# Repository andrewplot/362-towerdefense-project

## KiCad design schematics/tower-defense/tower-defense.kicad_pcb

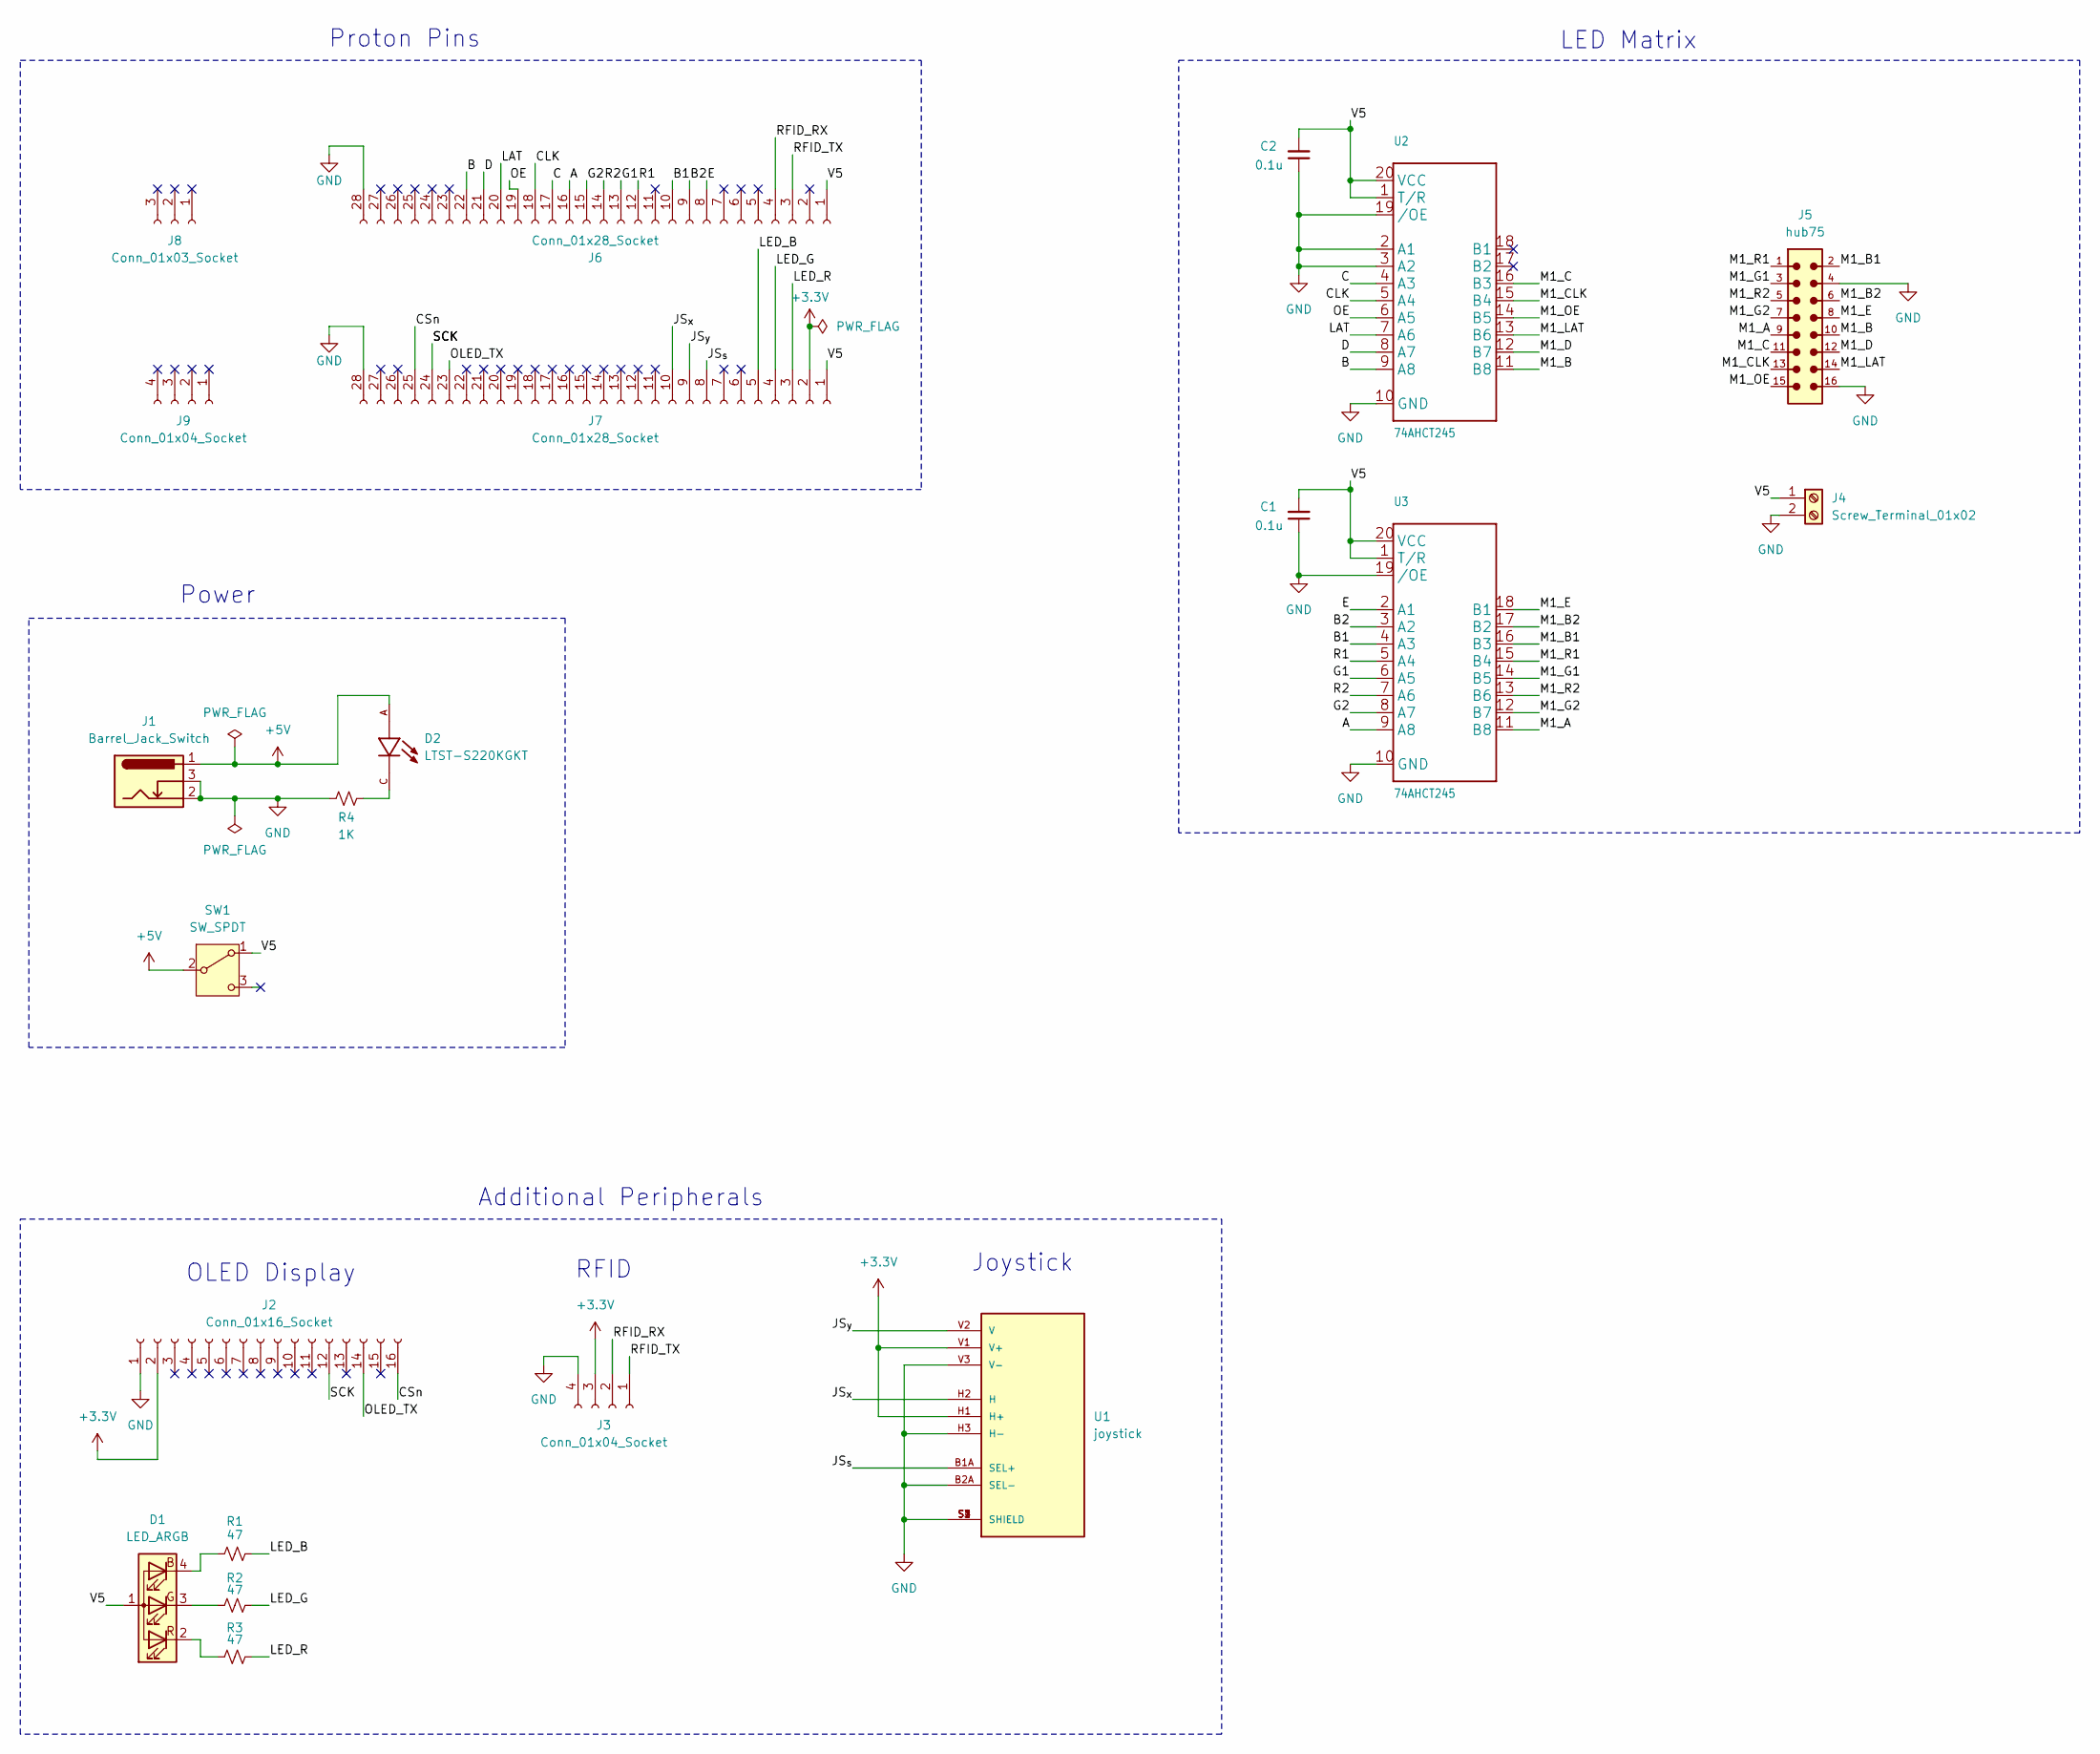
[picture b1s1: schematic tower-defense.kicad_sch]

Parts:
C1, C2: 0.1u; C_0603_1608Metric
D1: LED_ARGB; PinSocket_1x04_P2.54mm_Vertical
D2: LTST-S220KGKT; status_led; PARTREV D
J1: Barrel_Jack_Switch; barrel_jack
J2: Conn_01x16_Socket; PinSocket_1x16_P2.54mm_Vertical
J3: Conn_01x04_Socket; PinSocket_1x04_P2.54mm_Horizontal
J4: Screw_Terminal_01x02; screw-terminal
J5: hub75
J6, J7: Conn_01x28_Socket; PinSocket_1x28_P2.54mm_Vertical
J8: Conn_01x03_Socket; PinSocket_1x03_P2.54mm_Vertical
J9: Conn_01x04_Socket; PinSocket_1x04_P2.54mm_Vertical
R1, R2, R3: 47; R_0603_1608Metric
R4: 1K; R_0603_1608Metric
SW1: SW_SPDT; power_switch
U1: joystick; PARTREV N/A
U2, U3: 74AHCT245; 74HTC245

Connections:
+3.3V: J2.2, J3.3, J7.2, U1.H1 (H+), U1.V1 (V+)
+5V: D2.A, J1.1, SW1.2 (B)
/A: J6.16, U3.9 (A8)
/B: J6.22, U2.9 (A8)
/B1: J6.10, U3.4 (A3)
/B2: J6.9, U3.3 (A2)
/C: J6.17, U2.4 (A3)
/CLK: J6.18, U2.5 (A4)
/CSn: J2.16, J7.25
/D: J6.21, U2.8 (A7)
/E: J6.8, U3.2 (A1)
/G1: J6.13, U3.6 (A5)
/G2: J6.15, U3.8 (A7)
/JS_{s}: J7.8, U1.B1A (SEL+)
/JS_{x}: J7.10, U1.H2 (H)
/JS_{y}: J7.9, U1.V2 (V)
/LAT: J6.20, U2.7 (A6)
/LED_B: J7.5, R1.2
/LED_G: J7.4, R2.2
/LED_R: J7.3, R3.2
/M1_A: J5.9, U3.11 (B8)
/M1_B: J5.10, U2.11 (B8)
/M1_B1: J5.2, U3.16 (B3)
/M1_B2: J5.6, U3.17 (B2)
/M1_C: J5.11, U2.16 (B3)
/M1_CLK: J5.13, U2.15 (B4)
/M1_D: J5.12, U2.12 (B7)
/M1_E: J5.8, U3.18 (B1)
/M1_G1: J5.3, U3.14 (B5)
/M1_G2: J5.7, U3.12 (B7)
/M1_LAT: J5.14, U2.13 (B6)
/M1_OE: J5.15, U2.14 (B5)
/M1_R1: J5.1, U3.15 (B4)
/M1_R2: J5.5, U3.13 (B6)
/OE: J6.19, U2.6 (A5)
/OLED_TX: J2.14, J7.23
/R1: J6.12, U3.5 (A4)
/R2: J6.14, U3.7 (A6)
/RFID_RX: J3.2, J6.4
/RFID_TX: J3.1, J6.3
/SCK: J2.12, J7.24
/V5: C1.2, C2.2, D1.1 (A), J4.1, J6.1, J7.1, SW1.1 (A), U2.1 (T/R), U2.20 (VCC), U3.1 (T/R), U3.20 (VCC)
GND: C1.1, C2.1, J1.2, J1.3, J2.1, J3.4, J4.2, J5.4, J5.16, J6.28, J7.28, R4.1, U1.B2A (SEL-), U1.H3 (H-), U1.S1 (SHIELD), U1.S2 (SHIELD), U1.S3 (SHIELD), U1.S4 (SHIELD), U1.V3 (V-), U2.2 (A1), U2.3 (A2), U2.10 (GND), U2.19 (/OE), U3.10 (GND), U3.19 (/OE)
unnamed: D1.4 (BK), R1.1
unnamed: D1.3 (GK), R2.1
unnamed: D1.2 (RK), R3.1
unnamed: D2.C, R4.2

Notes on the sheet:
LED Matrix
Additional Peripherals
RFID
Power
OLED Display
Proton Pins
Joystick

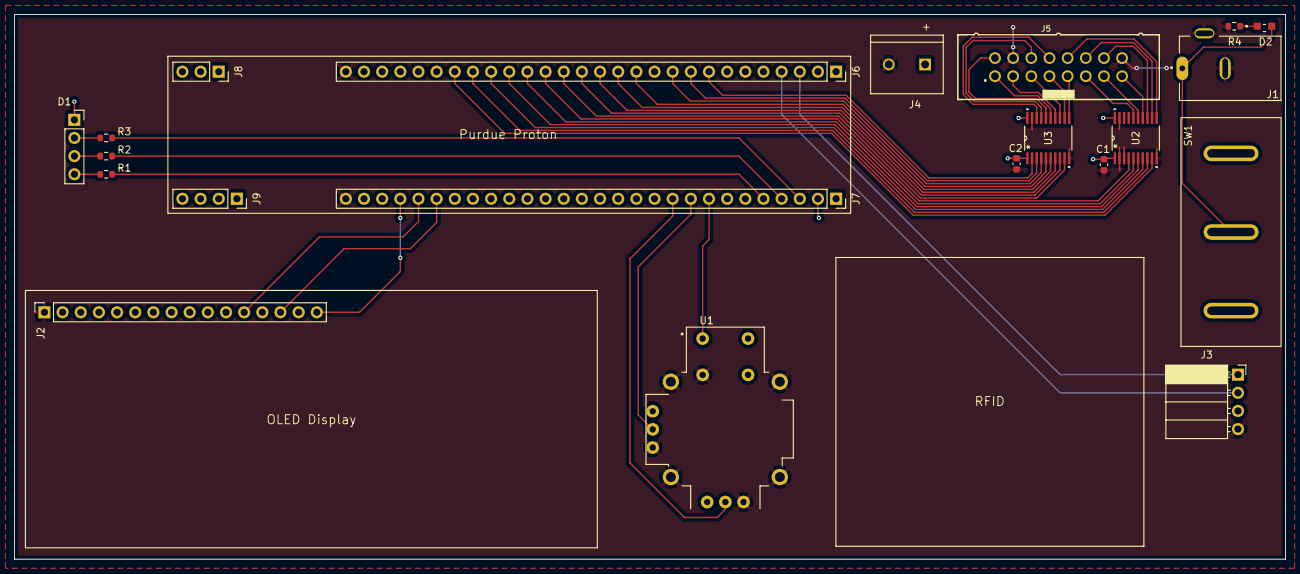
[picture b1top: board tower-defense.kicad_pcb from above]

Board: 2 copper layers, 177.8 x 76.2 mm, 21 parts (0 on the bottom side), 47 nets.

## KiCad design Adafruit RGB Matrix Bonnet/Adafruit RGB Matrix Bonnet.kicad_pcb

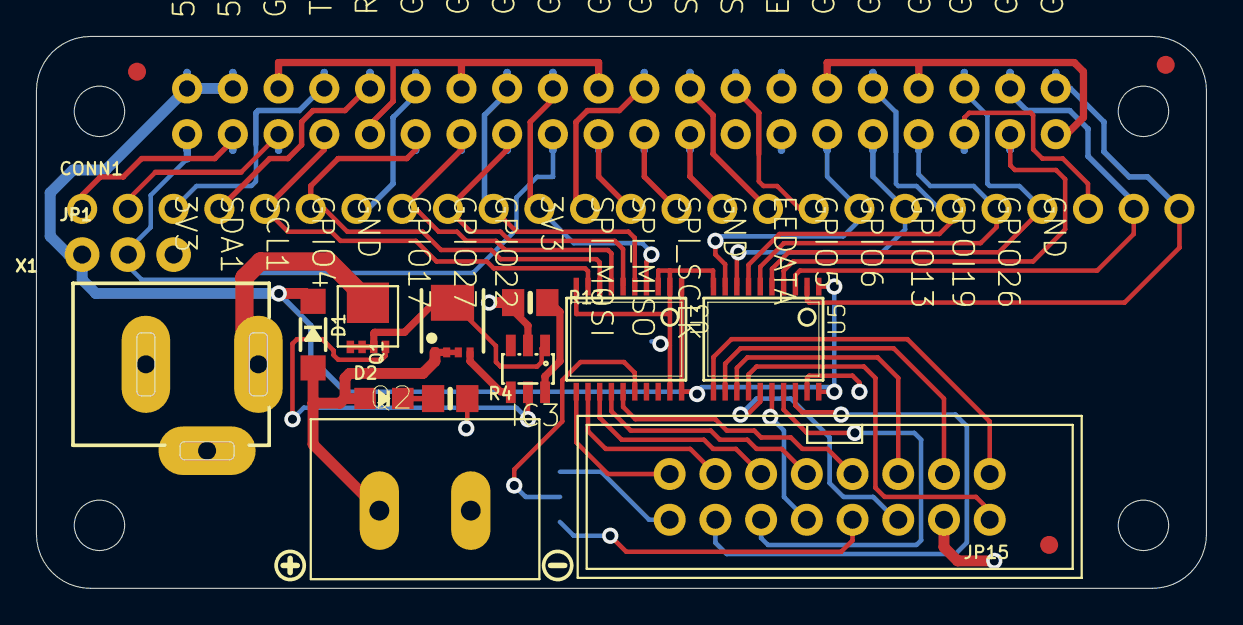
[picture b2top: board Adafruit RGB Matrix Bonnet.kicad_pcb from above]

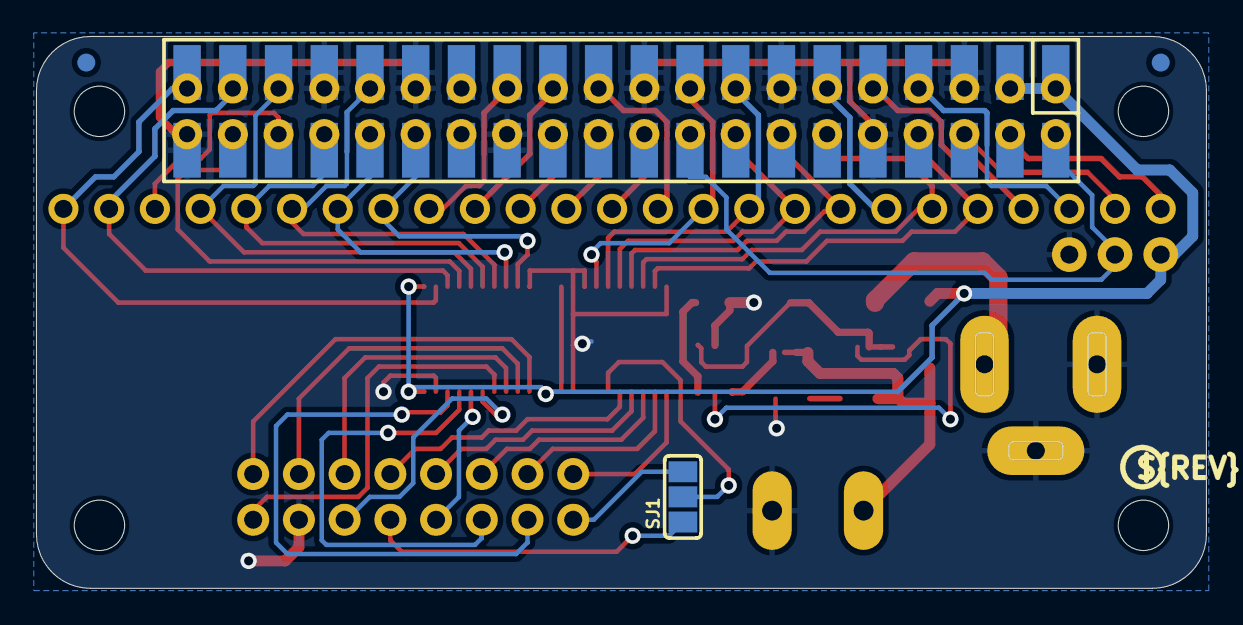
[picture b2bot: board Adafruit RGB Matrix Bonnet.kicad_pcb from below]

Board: 2 copper layers, 65.0 x 30.7 mm, 24 parts (3 on the bottom side), 54 nets.

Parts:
CONN1: HEADER-1X25; 1X25_ROUND_70MIL
D1: MBR120; SOD-123
D2: green; CHIPLED_0805_NOOUTLINE
FID1, FID2, FID3: FIDUCIAL_1MM
IC3: MAX4866T; SOT23-6
JP1: 1X03_ROUND_76
JP15: 2X08_SHROUDED
MATRIX_PWR0: PINHEAD; TERMBLOCK508
Q1: AON3414; POWERPAK-1212-8
Q2: AON7401; POWERDI3333
R4, R13: 1K; 0805-NO
RPI1: RASPBERRYPI_BPLUS_BONNET_THMSMT; PI_BONNET_THMSMT
SJ1: SOLDERJUMPER_2WAY_OPEN_NOPASTE
U3, U5: 74AHCT245; TSSOP20
U$1: BONNET_MATRIX_TOP
U$3: PCBFEAT-REV-056
U$6: BONNET_MATRIX_BOT
U$10: SYMBOL_PLUS
U$11: SYMBOL_MINUS
X1: 2.1mm DC; DCJACK_2MM_PTH

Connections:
3.3V: JP1.2, RPI1.1, RPI1.17, RPI1.S1, RPI1.S17
5.0V: D1.A, D2.A, MATRIX_PWR0.P$4, Q1.1, Q1.2, Q1.3
5VIN: Q2.5678, X1.PWR
+5V: D1.C, JP1.1, RPI1.2, RPI1.4, RPI1.S2, RPI1.S4, U3.1, U3.20, U5.1, U5.20
CLK: JP15.13, U3.12
EECLK: RPI1.28, RPI1.S28
EEDATA: RPI1.27, RPI1.S27
GND: IC3.2, JP1.3, JP15.4, MATRIX_PWR0.P$3, R4.2, R13.1, RPI1.6, RPI1.9, RPI1.14, RPI1.20, RPI1.25, RPI1.30, RPI1.34, RPI1.39, RPI1.S6, RPI1.S9, RPI1.S14, RPI1.S20, RPI1.S25, RPI1.S30, RPI1.S34, RPI1.S39, U3.2, U3.3, U3.10, U3.19, U5.10, U5.19, X1.GND, X1.GNDBREAK
GPIO4: CONN1.5, RPI1.7, RPI1.S7, U3.9
GPIO5: CONN1.18, RPI1.29, RPI1.S29, U5.9
GPIO6: CONN1.19, RPI1.31, RPI1.S31, U5.8
GPIO12: CONN1.20, RPI1.32, RPI1.S32, U5.7
GPIO13: CONN1.21, RPI1.33, RPI1.S33, U5.6
GPIO16: CONN1.22, RPI1.36, RPI1.S36, U5.5
GPIO17: CONN1.6, RPI1.11, RPI1.S11, U3.8
GPIO18: CONN1.7, RPI1.12, RPI1.S12
GPIO19: CONN1.23, RPI1.35, RPI1.S35
GPIO20: CONN1.24, RPI1.38, RPI1.S38, U5.3
GPIO21: CONN1.25, RPI1.40, RPI1.S40, U5.2
GPIO22: CONN1.9, RPI1.15, RPI1.S15, U3.6
GPIO23: CONN1.10, RPI1.16, RPI1.S16, U3.5
GPIO24: CONN1.11, RPI1.18, RPI1.S18, U3.4
GPIO25: CONN1.12, RPI1.22, RPI1.S22
GPIO26: RPI1.37, RPI1.S37, U5.4
GPIO27: CONN1.8, RPI1.13, RPI1.S13, U3.7
LAT: JP15.14, U5.18
M1_A: JP15.9, U3.14
M1_B: JP15.10, U5.16
M1_B1: JP15.3, U5.12
M1_B2: JP15.7, U3.15
M1_C: JP15.11, U3.13
M1_D: JP15.12, U5.17
M1_E: SJ1.2, U3.16
M1_E': JP15.8, SJ1.1
M1_E'': JP15.16, SJ1.3
M1_G1: JP15.2, U5.14
M1_G2: JP15.6, U5.15
M1_R1: JP15.1, U5.11
M1_R2: JP15.5, U5.13
unnamed: IC3.6, R13.2
unnamed: D2.C, R4.1
unnamed: IC3.1, Q1.5-8, Q2.1, Q2.2, Q2.3
unnamed: IC3.4, Q1.4
unnamed: IC3.5, Q2.4
OE: JP15.15, U3.11
RXD: CONN1.4, RPI1.10, RPI1.S10
SCL: CONN1.2, RPI1.5, RPI1.S5
SDA: CONN1.1, RPI1.3, RPI1.S3
SPI_CE0: CONN1.16, RPI1.24, RPI1.S24
SPI_CE1: CONN1.17, RPI1.26, RPI1.S26
SPI_MISO: CONN1.14, RPI1.21, RPI1.S21
SPI_MOSI: CONN1.13, RPI1.19, RPI1.S19
SPI_SCLK: CONN1.15, RPI1.23, RPI1.S23
TXD: CONN1.3, RPI1.8, RPI1.S8

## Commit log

2025-10-09 Added PlatformIO
2025-10-16 moved file
2025-10-16 Simulation Code for LED Matrix
2025-10-16 Add Simulation Folder
2025-10-16 joystick
2025-10-30 Finish joystick
2025-11-04 start schematic and matrix
2025-11-04 python skeleton
2025-11-04 pin selections
2025-11-06 Joystick sample
2025-11-06 frame renderer completed
2025-11-07 added enemies
2025-11-07 improved background
2025-11-07 work on colors, need to fix whitewashing
2025-11-08 asfd
2025-11-10 gpio pins change
2025-11-11 display finish
2025-11-11 oled update
2025-11-11 rfid
2025-11-11 organize schematics
2025-11-11 update matrix, integrate oled and joystick
2025-11-11 change
2025-11-11 updated joystick with deadzone
2025-11-11 update matrix
2025-11-11 update to cpp
2025-11-11 towers
2025-11-12 update mehehehe
2025-11-12 redid visuals
2025-11-12 added all tower and enemy types
2025-11-12 working on banner plane, finnicky
2025-11-13 fixed banner plane
2025-11-14 Started schematic
2025-11-14 update gitignore for file storage`
2025-11-17 complete pcb v1
2025-11-20 fixed helicopter crash
2025-11-20 pcb submission and update pins
2025-12-01 Changing RDIF Pins to 0 and 1
2025-12-01 buzzer files
2025-12-01 removed unsigned int
2025-12-01 pre-tgiving changes
2025-12-02 Char display CGRAM
2025-12-02 wave system
2025-12-02 Adding tunes
2025-12-02 header pseudcoode
2025-12-02 Switched the melodies from main to buzzer_pwm.c file
2025-12-02 implement rfid and buzzer
2025-12-02 c conversion test
2025-12-02 implement oled
2025-12-02 Added Melodies
2025-12-02 Changed Melody to be an octave higher
2025-12-02 implement buzzer
2025-12-02 implement matrix
2025-12-02 a shit ton of code and refactoring
2025-12-02 ready
2025-12-03 fix oled issue
2025-12-03 asdf
